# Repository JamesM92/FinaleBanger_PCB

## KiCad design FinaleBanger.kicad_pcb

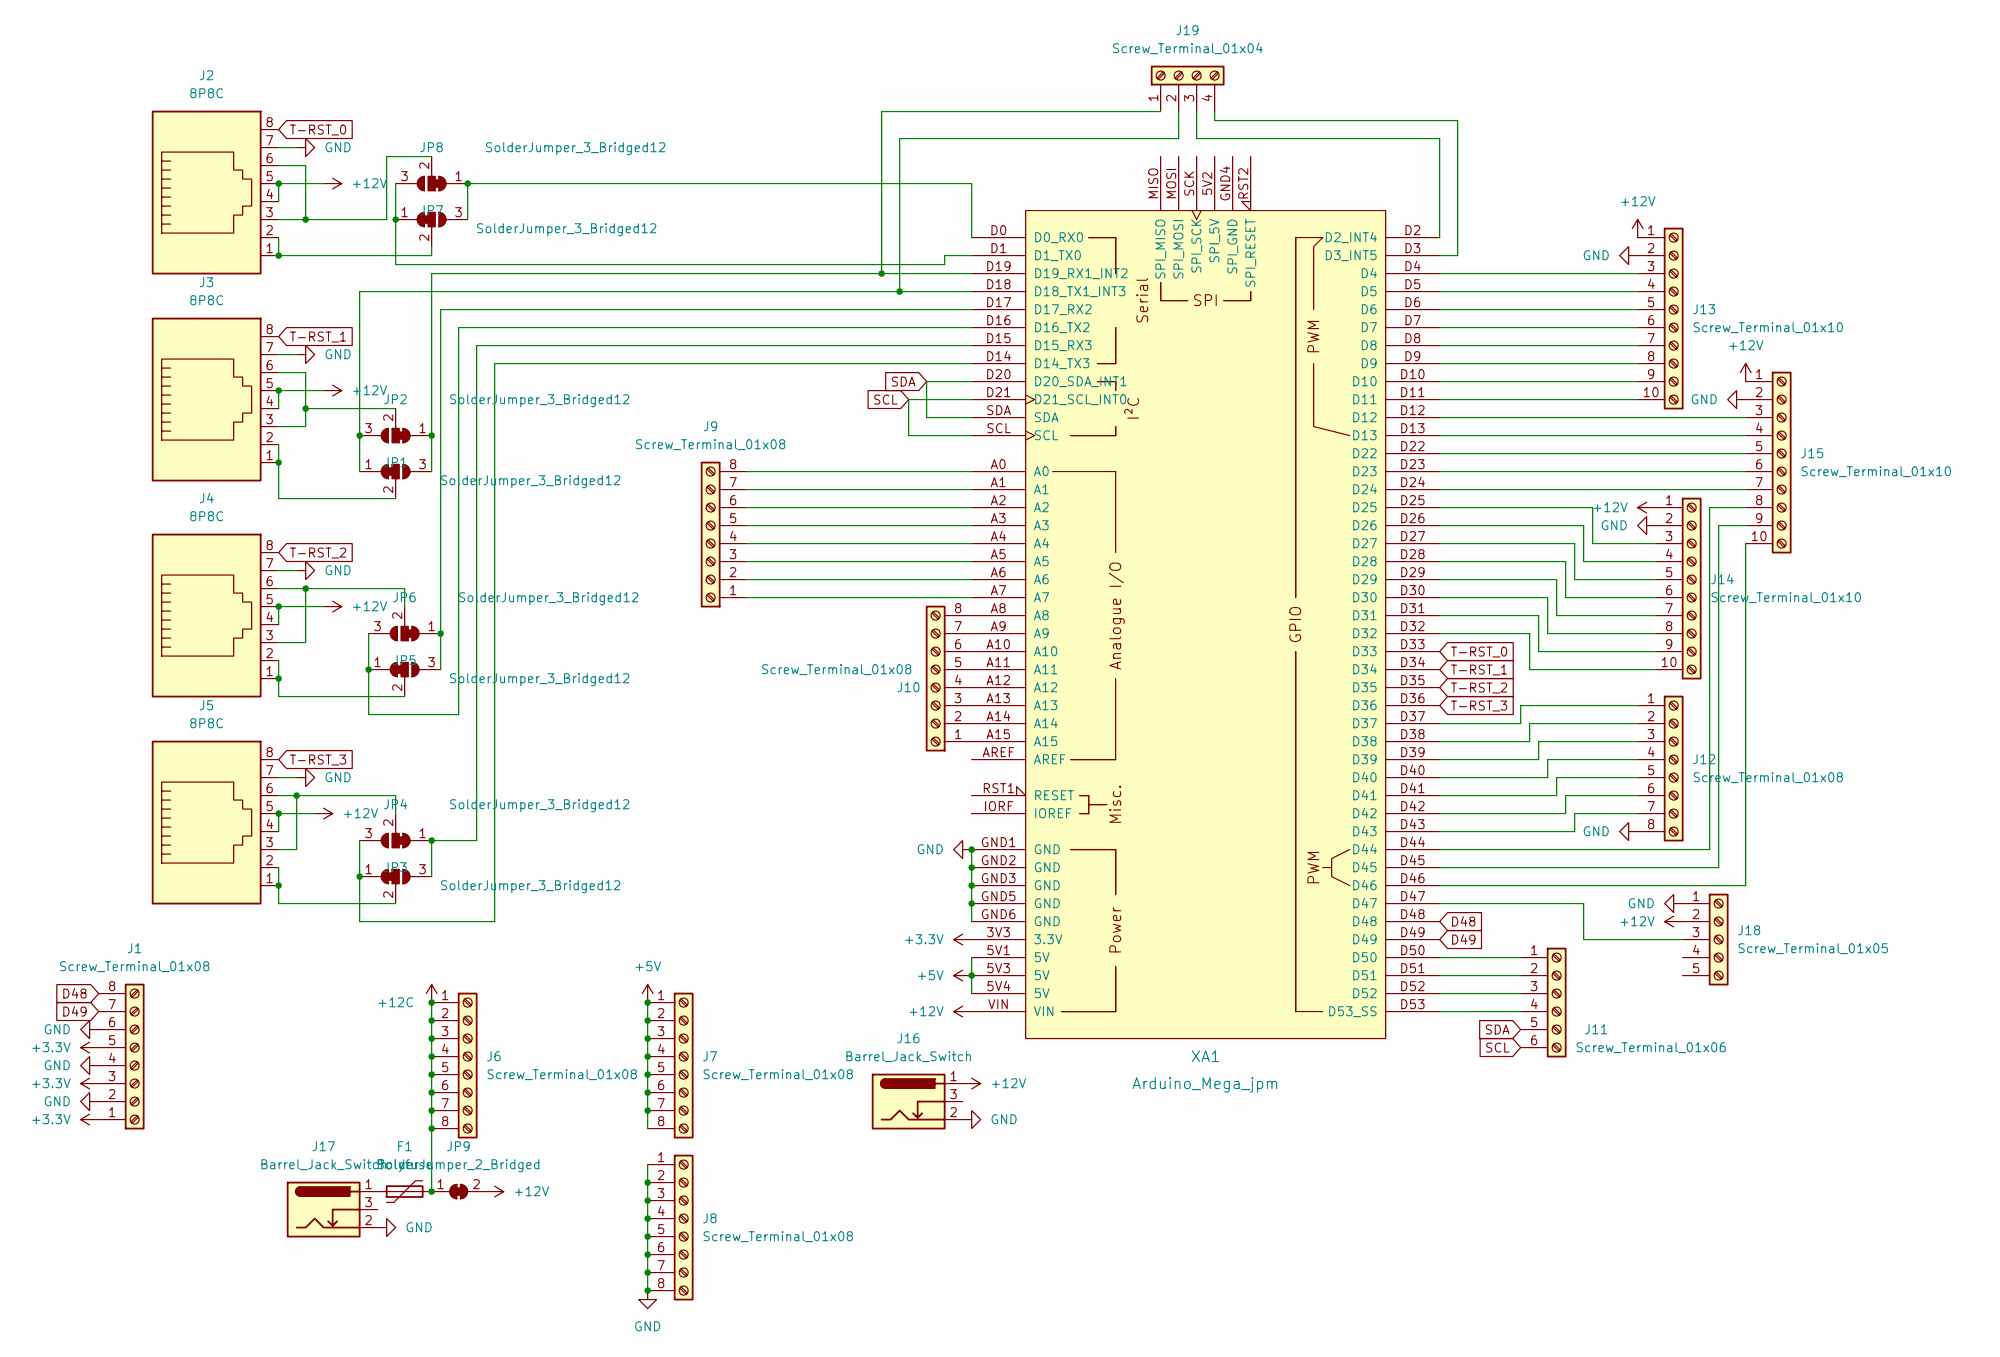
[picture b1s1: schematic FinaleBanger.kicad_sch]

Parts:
F1: Polyfuse; THT_JUMPER
J1, J6, J7, J8, J9, J10, J12: Screw_Terminal_01x08; TerminalBlock_RND_205-00051_1x08_P5.00mm_Horizontal
J2, J3, J4, J5: 8P8C; RJ45_OST_PJ012-8P8CX_Vertical
J11: Screw_Terminal_01x06; TerminalBlock_RND_205-00049_1x06_P5.00mm_Horizontal
J13, J14, J15: Screw_Terminal_01x10; PinHeader_1x10_P5.0mm_Horizontal
J16, J17: Barrel_Jack_Switch; Vertical-BarrelJack_54-00287
J18: Screw_Terminal_01x05; 691311500105
J19: Screw_Terminal_01x04; TerminalBlock_RND_205-00047_1x04_P5.00mm_Horizontal
JP1, JP2, JP3, JP4, JP5, JP6, JP7, JP8: SolderJumper_3_Bridged12; SolderJumper-3_P1.3mm_Bridged2Bar12_Pad1.0x1.5mm
JP9: SolderJumper_2_Bridged; SolderJumper-2_P1.3mm_Bridged_Pad1.0x1.5mm
XA1: Arduino_Mega_jpm; Arduino_Mega2560_Shield

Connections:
+3.3V: J1.1, J1.3, J1.5, XA1.3V3 (3.3V)
+5V: J7.1, J7.2, J7.3, J7.4, J7.5, J7.6, J7.7, J7.8, XA1.5V1 (5V), XA1.5V3 (5V), XA1.5V4 (5V)
+12C: F1.2, J6.1, J6.2, J6.3, J6.4, J6.5, J6.6, J6.7, J6.8, JP9.1 (A)
+12V: J2.4, J2.5, J3.4, J3.5, J4.4, J4.5, J5.4, J5.5, J13.1, J14.1, J15.1, J16.1, J18.2, JP9.2 (B), XA1.VIN
D48: J1.8, XA1.D48
D49: J1.7, XA1.D49
GND: J1.2, J1.4, J1.6, J2.7, J3.7, J4.7, J5.7, J8.1, J8.2, J8.3, J8.4, J8.5, J8.6, J8.7, J8.8, J12.8, J13.2, J14.2, J15.2, J16.2, J17.2, J18.1, XA1.GND1 (GND), XA1.GND2 (GND), XA1.GND3 (GND), XA1.GND5 (GND), XA1.GND6 (GND)
unnamed: F1.1, J17.1
unnamed: J2.1, J2.2, JP8.2 (C)
unnamed: J2.3, J2.6, JP7.2 (C)
unnamed: J3.1, J3.2, JP2.2 (C)
unnamed: J3.3, J3.6, JP1.2 (C)
unnamed: J4.1, J4.2, JP6.2 (C)
unnamed: J4.3, J4.6, JP5.2 (C)
unnamed: J5.1, J5.2, JP4.2 (C)
unnamed: J5.3, J5.6, JP3.2 (C)
unnamed: J9.1, XA1.A7
unnamed: J9.2, XA1.A6
unnamed: J9.3, XA1.A5
unnamed: J9.4, XA1.A4
unnamed: J9.5, XA1.A3
unnamed: J9.6, XA1.A2
unnamed: J9.7, XA1.A1
unnamed: J9.8, XA1.A0
unnamed: J10.1, XA1.A15
unnamed: J10.2, XA1.A14
unnamed: J10.3, XA1.A13
unnamed: J10.4, XA1.A12
unnamed: J10.5, XA1.A11
unnamed: J10.6, XA1.A10
unnamed: J10.7, XA1.A9
unnamed: J10.8, XA1.A8
unnamed: J11.1, XA1.D50
unnamed: J11.2, XA1.D51
unnamed: J11.3, XA1.D52
unnamed: J11.4, XA1.D53 (D53_SS)
unnamed: J12.1, XA1.D37
unnamed: J12.2, XA1.D38
unnamed: J12.3, XA1.D39
unnamed: J12.4, XA1.D40
unnamed: J12.5, XA1.D41
unnamed: J12.6, XA1.D42
unnamed: J12.7, XA1.D43
unnamed: J13.3, XA1.D4
unnamed: J13.4, XA1.D5
unnamed: J13.5, XA1.D6
unnamed: J13.6, XA1.D7
unnamed: J13.7, XA1.D8
unnamed: J13.8, XA1.D9
unnamed: J13.9, XA1.D10
unnamed: J13.10, XA1.D11
unnamed: J14.3, XA1.D25
unnamed: J14.4, XA1.D26
unnamed: J14.5, XA1.D27
unnamed: J14.6, XA1.D28
unnamed: J14.7, XA1.D29
unnamed: J14.8, XA1.D30
unnamed: J14.9, XA1.D31
unnamed: J14.10, XA1.D32
unnamed: J15.3, XA1.D12
unnamed: J15.4, XA1.D13
unnamed: J15.5, XA1.D22
unnamed: J15.6, XA1.D23
unnamed: J15.7, XA1.D24
unnamed: J15.8, XA1.D44
unnamed: J15.9, XA1.D45
unnamed: J15.10, XA1.D46
unnamed: J18.3, XA1.D47
unnamed: J19.1, JP1.1 (A), JP2.3 (B), XA1.D19 (D19_RX1_INT2)
unnamed: J19.2, JP1.3 (B), JP2.1 (A), XA1.D18 (D18_TX1_INT3)
unnamed: J19.3, XA1.D2 (D2_INT4)
unnamed: J19.4, XA1.D3 (D3_INT5)
unnamed: JP3.1 (A), JP4.3 (B), XA1.D15 (D15_RX3)
unnamed: JP3.3 (B), JP4.1 (A), XA1.D14 (D14_TX3)
unnamed: JP5.1 (A), JP6.3 (B), XA1.D17 (D17_RX2)
unnamed: JP5.3 (B), JP6.1 (A), XA1.D16 (D16_TX2)
unnamed: JP7.1 (A), JP8.3 (B), XA1.D0 (D0_RX0)
unnamed: JP7.3 (B), JP8.1 (A), XA1.D1 (D1_TX0)
SCL: J11.6, XA1.D21 (D21_SCL_INT0), XA1.SCL
SDA: J11.5, XA1.D20 (D20_SDA_INT1), XA1.SDA
T-RST_0: J2.8, XA1.D33
T-RST_1: J3.8, XA1.D34
T-RST_2: J4.8, XA1.D35
T-RST_3: J5.8, XA1.D36

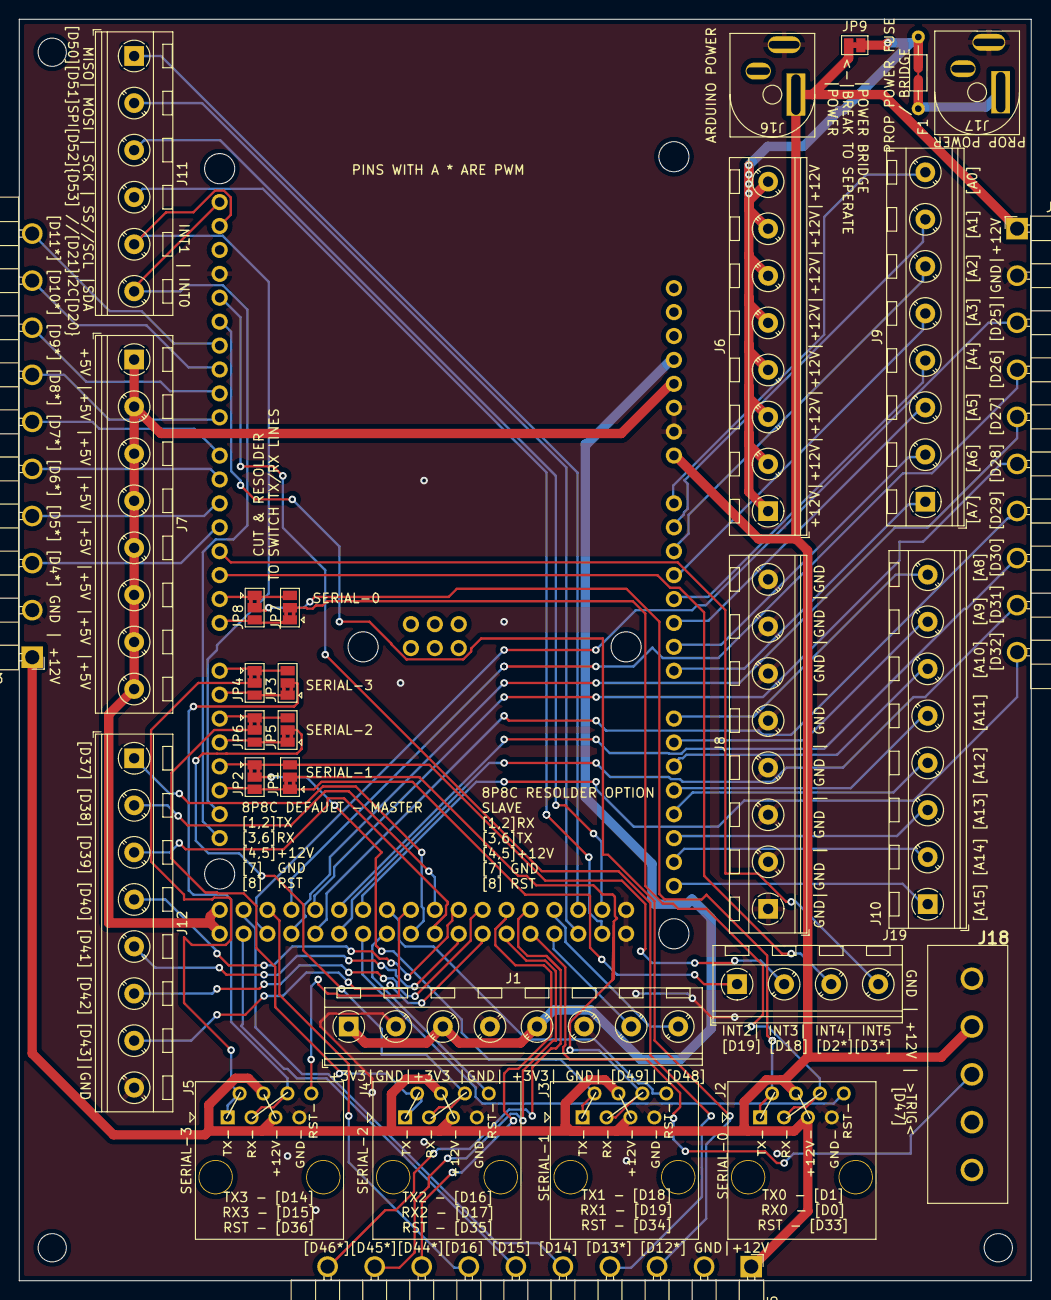
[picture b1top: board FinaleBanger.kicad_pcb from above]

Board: 2 copper layers, 107.5 x 134.0 mm, 30 parts (1 on the bottom side), 84 nets.

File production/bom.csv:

Designator,Footprint,Quantity,Value,LCSC Part #
J1,TerminalBlock_RND_205-00051_1x08_P5.00mm_Horizontal,1,Screw_Terminal_01x08,
J9,TerminalBlock_RND_205-00051_1x08_P5.00mm_Horizontal,1,Screw_Terminal_01x08,
JP3,SolderJumper-3_P1.3mm_Bridged2Bar12_Pad1.0x1.5mm,1,SolderJumper_3_Bridged12,
J14,PinHeader_1x10_P5.0mm_Horizontal,1,Screw_Terminal_01x10,
JP5,SolderJumper-3_P1.3mm_Bridged2Bar12_Pad1.0x1.5mm,1,SolderJumper_3_Bridged12,
JP4,SolderJumper-3_P1.3mm_Bridged2Bar12_Pad1.0x1.5mm,1,SolderJumper_3_Bridged12,
J2,RJ45_OST_PJ012-8P8CX_Vertical,1,8P8C,
J13,PinHeader_1x10_P5.0mm_Horizontal,1,Screw_Terminal_01x10,
J5,RJ45_OST_PJ012-8P8CX_Vertical,1,8P8C,
J15,PinHeader_1x10_P5.0mm_Horizontal,1,Screw_Terminal_01x10,
J7,TerminalBlock_RND_205-00051_1x08_P5.00mm_Horizontal,1,Screw_Terminal_01x08,
JP8,SolderJumper-3_P1.3mm_Bridged2Bar12_Pad1.0x1.5mm,1,SolderJumper_3_Bridged12,
J17,Vertical-BarrelJack_54-00287,1,Barrel_Jack_Switch,
J11,TerminalBlock_RND_205-00049_1x06_P5.00mm_Horizontal,1,Screw_Terminal_01x06,
J8,TerminalBlock_RND_205-00051_1x08_P5.00mm_Horizontal,1,Screw_Terminal_01x08,
J12,TerminalBlock_RND_205-00051_1x08_P5.00mm_Horizontal,1,Screw_Terminal_01x08,
J6,TerminalBlock_RND_205-00051_1x08_P5.00mm_Horizontal,1,Screw_Terminal_01x08,
J3,RJ45_OST_PJ012-8P8CX_Vertical,1,8P8C,
JP2,SolderJumper-3_P1.3mm_Bridged2Bar12_Pad1.0x1.5mm,1,SolderJumper_3_Bridged12,
JP6,SolderJumper-3_P1.3mm_Bridged2Bar12_Pad1.0x1.5mm,1,SolderJumper_3_Bridged12,
JP1,SolderJumper-3_P1.3mm_Bridged2Bar12_Pad1.0x1.5mm,1,SolderJumper_3_Bridged12,
JP7,SolderJumper-3_P1.3mm_Bridged2Bar12_Pad1.0x1.5mm,1,SolderJumper_3_Bridged12,
J19,TerminalBlock_RND_205-00047_1x04_P5.00mm_Horizontal,1,Screw_Terminal_01x04,
J10,TerminalBlock_RND_205-00051_1x08_P5.00mm_Horizontal,1,Screw_Terminal_01x08,
JP9,SolderJumper-2_P1.3mm_Bridged_Pad1.0x1.5mm,1,SolderJumper_2_Bridged,
J18,691311500105,1,Screw_Terminal_01x05,
J16,Vertical-BarrelJack_54-00287,1,Barrel_Jack_Switch,
J4,RJ45_OST_PJ012-8P8CX_Vertical,1,8P8C,
F1,THT_JUMPER,1,Polyfuse,
XA1,Arduino_Mega2560_Shield,1,Arduino_Mega_jpm,

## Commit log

2022-10-05 updated pdf
